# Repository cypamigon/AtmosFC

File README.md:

# AtmosFC

AtmosFC is an open-hardware quadcopter flight controller designed in KiCad. Powered by an STM32G4 MCU, it integrates high-performance sensors and peripherals, and is fully compatible with Betaflight (≥ 4.5).

## Table of Contents
- [Features](#features)
- [Input / Output](#input--output)
- [Hardware Architecture](#hardware-architecture)
- [Flashing Betaflight](#flashing-betaflight)
- [Notes](#notes)
- [Gallery](#gallery)
- [Repository Structure](#repository-structure)
- [License](#license)

## Features

- **MCU**: STM32G473CEU6
- **IMU**: ICM-468-P
- **Barometer**: DPS-386
- **OSD**: MAX7456 for analog on-screen display
- **Blackbox**: 32MB onboard flash memory for log recording
- **Power input**: Up to 8S
    > ⚠️   The board has been tested with 6S LiPo batteries. The onboard MAX25232 buck regulator can theoretically support up to 36 V (~ 8S LiPo), but this has not been tested. Use higher voltages at your own risk.
- **Power monitoring**: Battery voltage and current sensing
- **Status indicators**: Green, Blue, and Amber LEDs
- **Dimensions**: 40x40mm
- **Mounting holes**: 30.5×30.5 mm (M4 holes for silicone inserts with M3 screws)
- **Weight**: 8.2g

## Input / Output 

- **USB connector**: USB Type-C
- **Motor outputs**: x4
- **ESC**: Current sensing and telemetry
- **UARTs**: x3
- **I2C**: Yes
- **Video Input / Video Output with OSD** 
- **5V outputs**: up to 3A total 
- **Buzzer output**

## Hardware Architecture

The block diagram below shows the main hardware components and their interconnections.

##  Flashing Betaflight

AtmosFC runs **Betaflight ≥ 4.5**. You can either flash the precompiled Betaflight 4.5 firmware or build the latest from source.

### Option 1 – Using the provided firmware
1. Open **Betaflight Configurator**.  
   If you don’t have it installed, get the latest version here : [Betaflight Configurator Releases](https://github.com/betaflight/betaflight-configurator/releases/latest)
3. Connect AtmosFC via USB-C.
4. If required, enter DFU mode (hold the BOOT button while plugging in USB).
5. In the Betaflight Configurator, go to **Firmware Flasher → Load firmware [Local]** and select the file `betaflight_4.5.0_ATMOSFC.hex` in `betaflight_config/`.
6. Click **Flash Firmware** and wait for the board to reboot.

### Option 2 – Building from Source

1. Clone the [Betaflight Repository](https://github.com/betaflight/betaflight) and install the required toolchain. Follow the official setup guide for your OS : [Betaflight Building Docs](https://betaflight.com/docs/category/building).
2. In the Betaflight root directory, update the target list by running:
```
> make configs
```
3. Add the AtmosFC board configuration by copying the folder `betaflight_config/ATMOSFC/` into `betaflight/src/config/configs`.
4. Build the firmware for AtmosFC target.
```
> make ATMOSFC
```
5. The compiled `.hex` file will be located under `betaflight/obj/`.
Flash it using **Betaflight Configurator** (follow the steps from Option 1).

## Notes 
- The board has been **successfully tested with Betaflight 4.5**. All basic functions, including motor outputs, sensors, LEDs, were working correctly.
- **I did not test the OSD feature**, as I was flying using digital FPV goggles instead of analog video.
- There is a small **voltage drop on the VBAT measurement** (~0.2-0.3V) due to the Schottky diode used for reverse polarity protection.  
  - This can be compensated either by applying a software offset in Betaflight, or by using an alternative reverse polarity protection method, such as a MOSFET-based circuit

## Gallery

<p align="center">
  
    <br>
  
    <br>
  
    <br>
  
    <br>
  
</p>

## Repository Structure

The repository is organized as follows:

``` bash
├── hardware/             
│   ├── atmos_fc/           # KiCad project files (.kicad_pcb, .sch, etc.)  
│   ├── assembly/           # Fabrication files (Gerber, BOM)
│   └── lib/                # Custom footprints, symbols, 3D models
├── betaflight_config/
│   ├── ATMOSFC/            # Board configuration for Betaflight ≥ 4.5
│   └── betaflight_4.5.0_ATMOSFC.hex    # Precompiled Betaflight 4.5 firmware
├── documentation/          # Schematic (.pdf), images, logo, block diagram
└── README.md
```

##  License

This project is released under the **[MIT License](LICENSE.txt)**.  
You are free to use, modify, and distribute it.

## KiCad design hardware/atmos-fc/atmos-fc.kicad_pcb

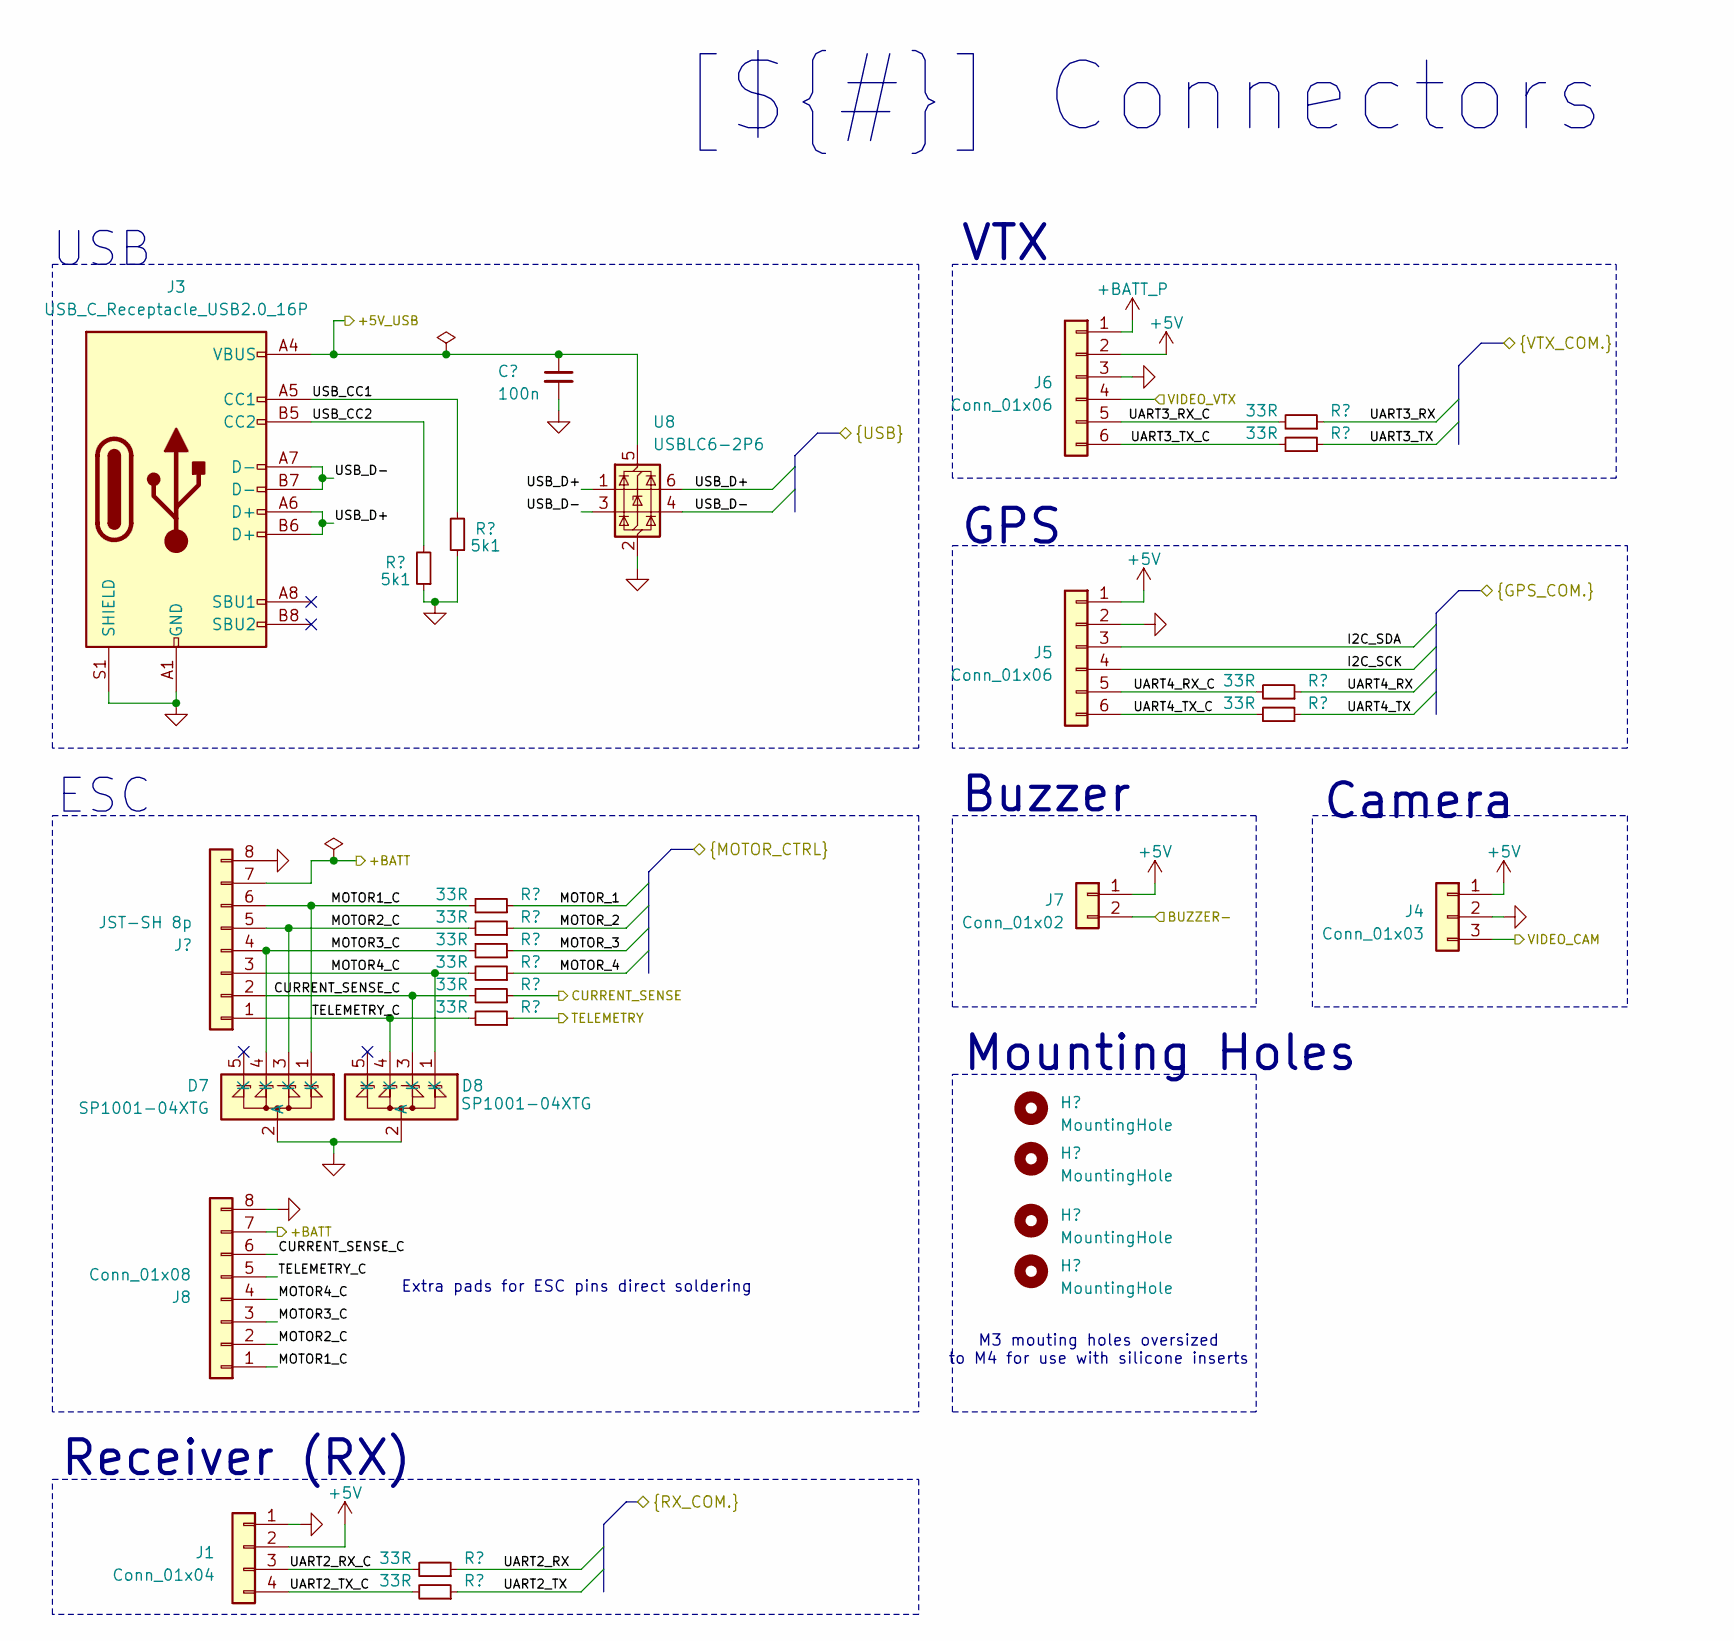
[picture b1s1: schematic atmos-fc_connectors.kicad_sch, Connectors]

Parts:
C34: 100n; C_0402_1005Metric; Mfr Part Number MSASE105SB7104KFNA01
D7, D8: SP1001-04XTG; SOT-553; Mfr Part Number SP1001-04XTG
H1, H2, H3, H4: MountingHole; MountingHole_4.3mm_M4
J1: Conn_01x04; SolderWirePads-2x2
J2: JST-SH 8p; JST_SR_SM08B-SRSS-TB; Mfr Part Number SM08B-SRSS-TB
J3: USB_C_Receptacle_USB2.0_16P; USB_C_Receptacle_GCT_USB4105-xx-A_16P_TopMnt_Horizontal; Mfr Part Number USB4105-GF-A
J4: Conn_01x03; SolderWirePads-1x3
J5, J6: Conn_01x06; SolderWirePads-1x6
J7: Conn_01x02; SolderWirePads-2x1
J8: Conn_01x08; SolderWirePads-2x4
R25, R26: 5k1; R_0402_1005Metric; Mfr Part Number CRCW04025K10FKED
R27, R28, R29, R30, R31, R32, R33, R34, R35, R36, R37, R38: 33R; R_0402_1005Metric; Mfr Part Number CRCW040220K0FKED
U8: USBLC6-2P6; SOT-666; Mfr Part Number USBLC6-2P6

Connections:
+5V: J1.2, J4.1, J5.1, J6.2, J7.1; also elsewhere on the board
+BATT_P: J6.1; also elsewhere on the board
/Connectors/+5V_USB: C34.1, J3.A4 (VBUS), J3.A9 (VBUS), J3.B4 (VBUS), J3.B9 (VBUS), U8.5 (VBUS); also elsewhere on the board
/Connectors/+BATT: J2.7, J8.7; also elsewhere on the board
/Connectors/BUZZER-: J7.2; also elsewhere on the board
/Connectors/CURRENT_SENSE: R31.1; also elsewhere on the board
/Connectors/CURRENT_SENSE_C: D8.3 (K), J2.2, J8.6, R31.2
/Connectors/I2C_SCK: J5.4; also elsewhere on the board
/Connectors/I2C_SDA: J5.3; also elsewhere on the board
/Connectors/MOTOR1_C: D7.1 (K), J2.6, J8.1, R27.2
/Connectors/MOTOR2_C: D7.3 (K), J2.5, J8.2, R28.2
/Connectors/MOTOR3_C: D7.4 (K), J2.4, J8.3, R29.2
/Connectors/MOTOR4_C: D8.1 (K), J2.3, J8.4, R30.2
/Connectors/MOTOR_1: R27.1; also elsewhere on the board
/Connectors/MOTOR_2: R28.1; also elsewhere on the board
/Connectors/MOTOR_3: R29.1; also elsewhere on the board
/Connectors/MOTOR_4: R30.1; also elsewhere on the board
/Connectors/TELEMETRY: R32.1; also elsewhere on the board
/Connectors/TELEMETRY_C: D8.4 (K), J2.1, J8.5, R32.2
/Connectors/UART2_RX: R33.1; also elsewhere on the board
/Connectors/UART2_RX_C: J1.3, R33.2
/Connectors/UART2_TX: R34.1; also elsewhere on the board
/Connectors/UART2_TX_C: J1.4, R34.2
/Connectors/UART3_RX: R37.1; also elsewhere on the board
/Connectors/UART3_RX_C: J6.5, R37.2
/Connectors/UART3_TX: R38.1; also elsewhere on the board
/Connectors/UART3_TX_C: J6.6, R38.2
/Connectors/UART4_RX: R35.1; also elsewhere on the board
/Connectors/UART4_RX_C: J5.5, R35.2
/Connectors/UART4_TX: R36.1; also elsewhere on the board
/Connectors/UART4_TX_C: J5.6, R36.2
/Connectors/USB_CC1: J3.A5 (CC1), R26.2
/Connectors/USB_CC2: J3.B5 (CC2), R25.2
/Connectors/USB_D+: J3.A6 (D+), J3.B6 (D+), U8.1 (I/O1), U8.6 (I/O1); also elsewhere on the board
/Connectors/USB_D-: J3.A7 (D-), J3.B7 (D-), U8.3 (I/O2), U8.4 (I/O2); also elsewhere on the board
/Connectors/VIDEO_CAM: J4.3; also elsewhere on the board
/Connectors/VIDEO_VTX: J6.4; also elsewhere on the board
GND: C34.2, D7.2 (A), D8.2 (A), J1.1, J2.8, J3.A1 (GND), J3.A12 (GND), J3.B1 (GND), J3.B12 (GND), J3.S1 (SHIELD), J4.2, J5.2, J6.3, J8.8, R25.1, R26.1, U8.2 (GND); also elsewhere on the board

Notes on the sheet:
[${#}] ${TITLE}
Camera
M3 mouting holes oversized to M4 for use with silicone inserts
Mounting Holes
Receiver (RX)
ESC
Buzzer
VTX
Extra pads for ESC pins direct soldering
GPS
USB

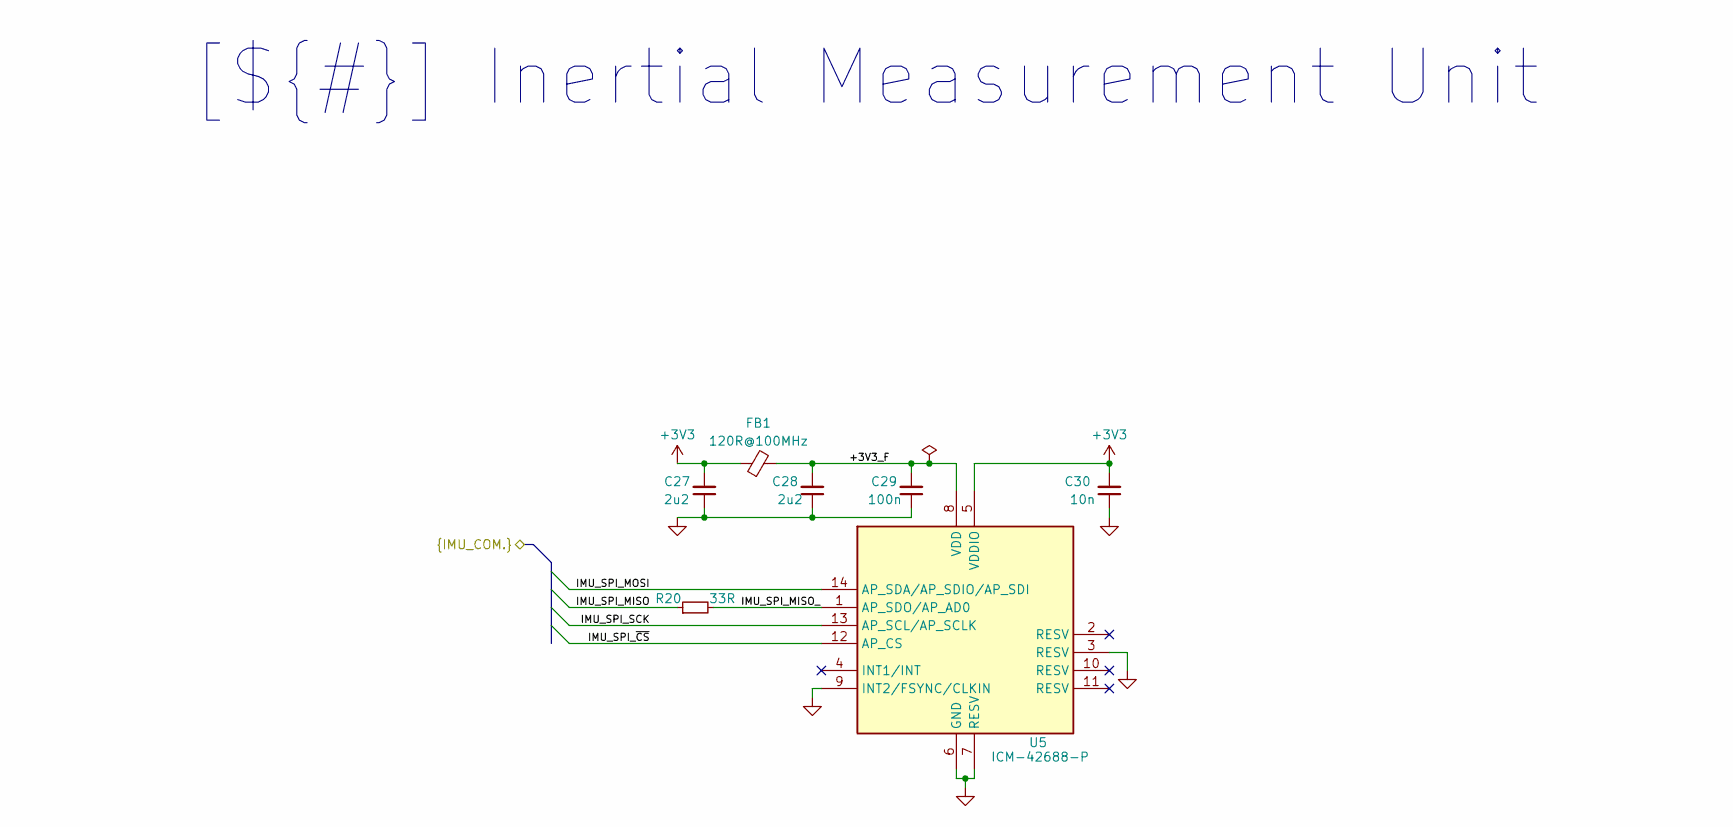
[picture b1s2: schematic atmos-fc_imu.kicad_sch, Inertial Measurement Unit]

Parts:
C27, C28: 2u2; C_0402_1005Metric; Mfr Part Number GRM155C71A225KE11D
C29: 100n; C_0402_1005Metric; Mfr Part Number MSASE105SB7104KFNA01
C30: 10n; C_0402_1005Metric; Mfr Part Number GRM1555C1E103GE01D
FB1: 120R@100MHz; L_0402_1005Metric; Mfr Part Number BLM15PX121BH1D
R20: 33R; R_0402_1005Metric; Mfr Part Number CRCW040220K0FKED
U5: ICM-42688-P; Mfr Part Number ICM-42688-P

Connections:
+3V3: C27.2, C30.2, FB1.1, U5.5 (VDDIO); also elsewhere on the board
/IMU/+3V3_F: C28.2, C29.2, FB1.2, U5.8 (VDD)
/IMU/IMU_INT: U5.4 (INT1/INT); also elsewhere on the board
/IMU/IMU_SPI_MISO: R20.1; also elsewhere on the board
/IMU/IMU_SPI_MISO_: R20.2, U5.1 (AP_SDO/AP_AD0)
/IMU/IMU_SPI_MOSI: U5.14 (AP_SDA/AP_SDIO/AP_SDI); also elsewhere on the board
/IMU/IMU_SPI_SCK: U5.13 (AP_SCL/AP_SCLK); also elsewhere on the board
/IMU/IMU_SPI_~CS: U5.12 (AP_CS); also elsewhere on the board
GND: C27.1, C28.1, C29.1, C30.1, U5.3 (RESV), U5.6 (GND), U5.7 (RESV), U5.9 (INT2/FSYNC/CLKIN); also elsewhere on the board

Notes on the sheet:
[${#}] ${TITLE}

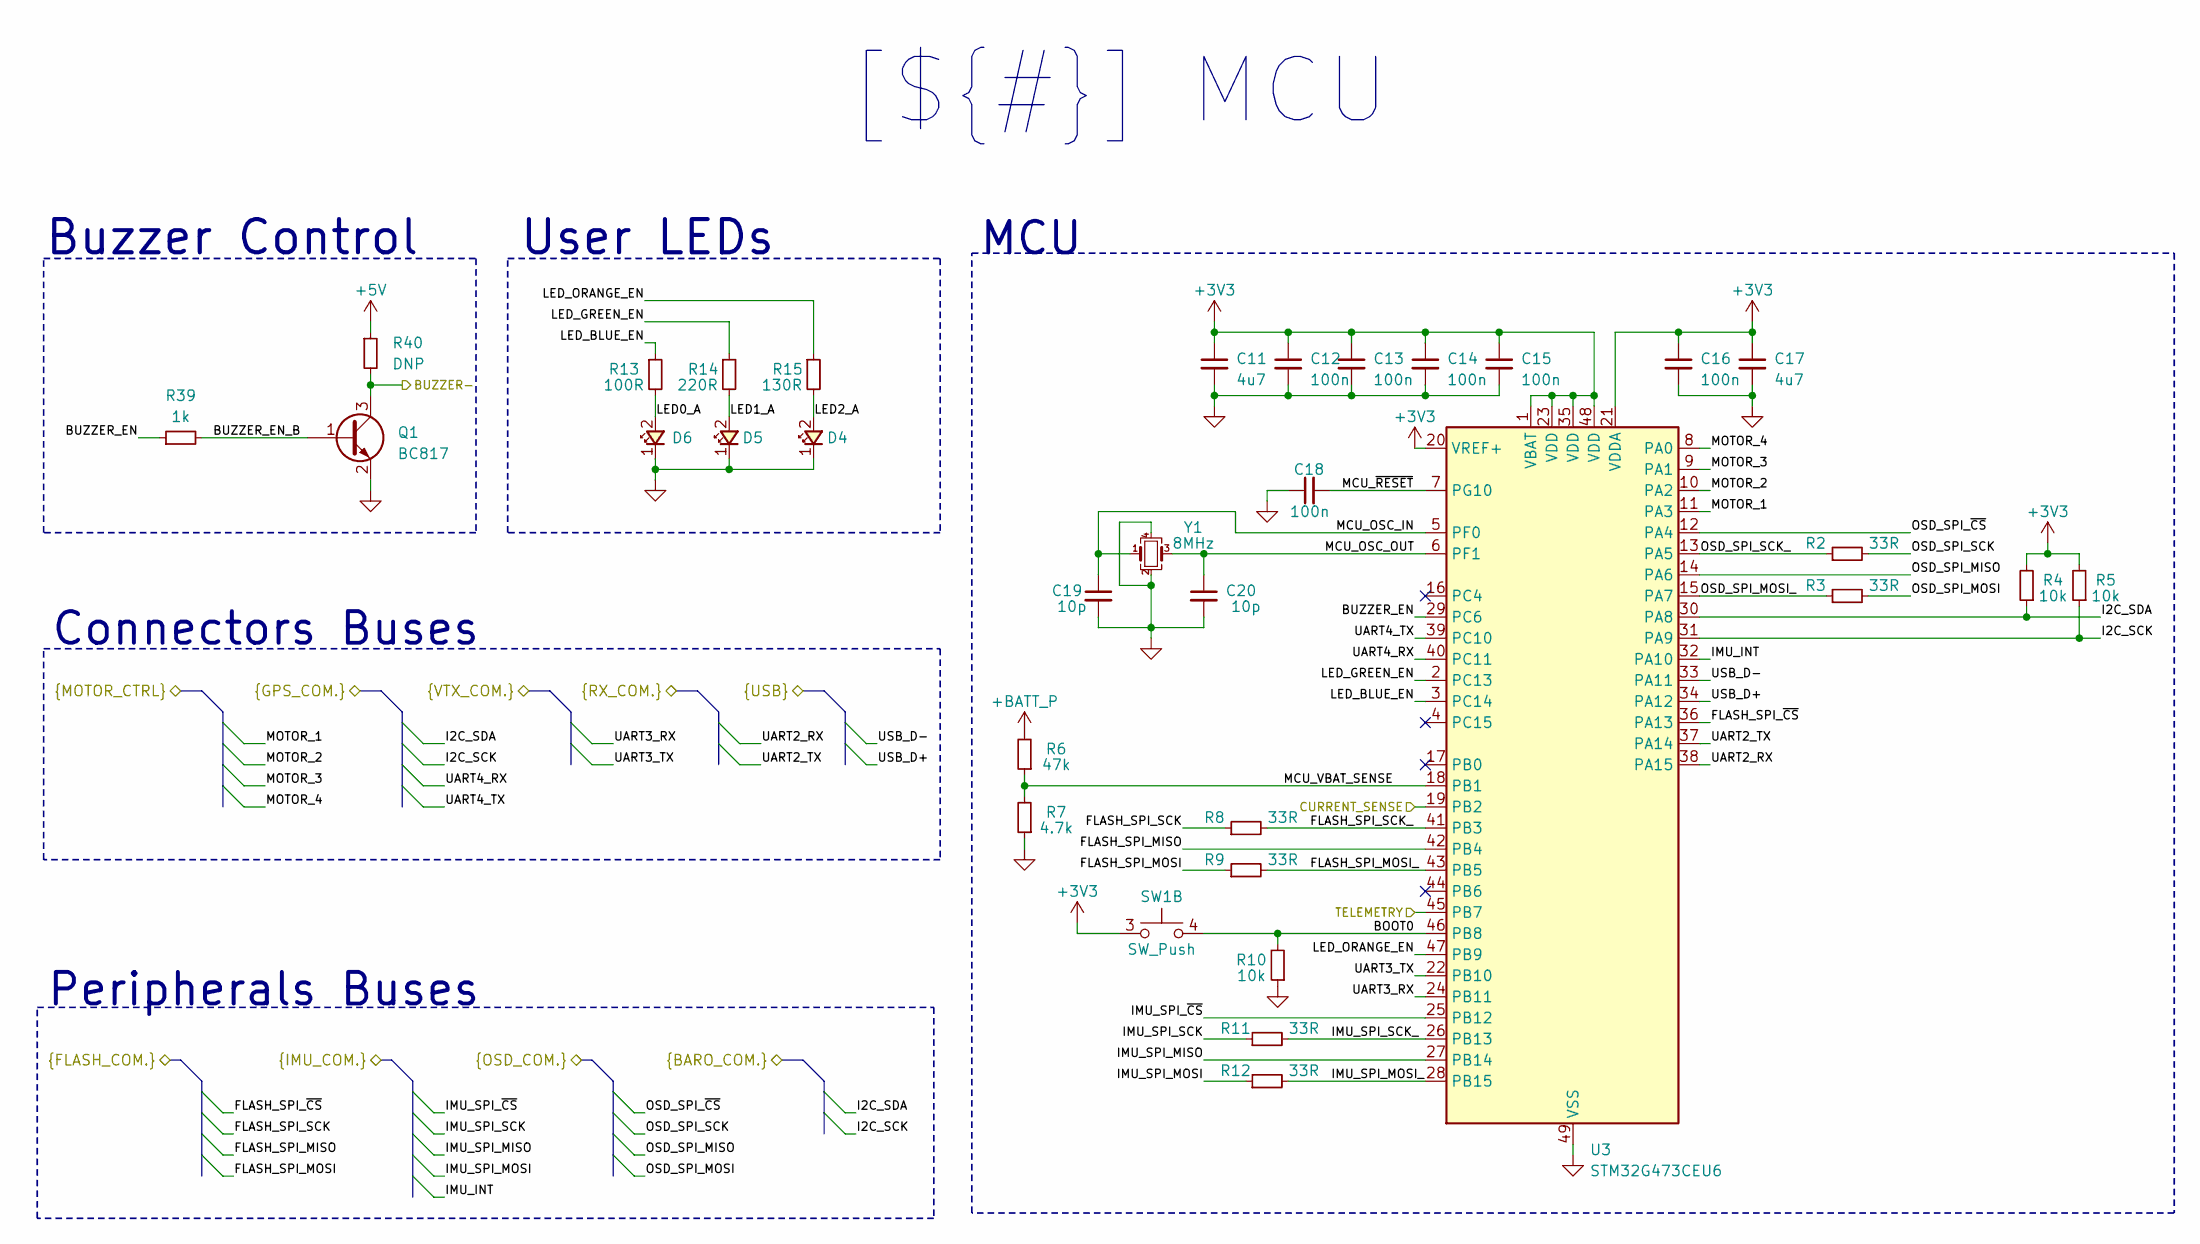
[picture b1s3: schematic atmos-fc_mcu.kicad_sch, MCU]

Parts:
C11, C17: 4u7; C_0603_1608Metric; Mfr Part Number GRM188Z71C475KE21J
C12, C13, C14, C15, C16, C18: 100n; C_0402_1005Metric; Mfr Part Number MSASE105SB7104KFNA01
C19, C20: 10p; C_0402_1005Metric; Mfr Part Number GRM1555C1H100JA01D
D4: LED_0603_1608Metric; Mfr Part Number LO Q976-PS-25
D5: LED_0603_1608Metric; Mfr Part Number LT Q39G-Q1OO-25-1
D6: LED_0603_1608Metric; Mfr Part Number LB Q39G-N1OO-35-1
Q1: BC817; DFN1010D-3; Mfr Part Number BC817-40QBH-QZ
R2, R3, R8, R9, R11, R12: 33R; R_0402_1005Metric; Mfr Part Number CRCW040220K0FKED
R4, R5, R10: 10k; R_0402_1005Metric; Mfr Part Number CRCW040210K0FKEDC
R6: 47k; R_0402_1005Metric; Mfr Part Number CRCW040247K0FKEDC
R7: 4.7k; R_0402_1005Metric; Mfr Part Number CRCW04024K70FKEDC
R13: 100R; R_0402_1005Metric; Mfr Part Number CRCW0402100RFKEDC
R14: 220R; R_0402_1005Metric; Mfr Part Number CRCW0402220RFKED
R15: 130R; R_0402_1005Metric; Mfr Part Number CRCW0402130RFKEDC
R39: 1k; R_0402_1005Metric; Mfr Part Number CRCW04021K00FKED
R40: DNP; R_0402_1005Metric
SW1: SW_Push; Wurth_436331045822; Mfr Part Number 436331045822
U3: STM32G473CEU6; QFN-48-1EP_7x7mm_P0.5mm_EP5.6x5.6mm; Mfr Part Number STM32G473CEU6
Y1: 8MHz; Crystal_SMD_ECS_ECX33_4Pin_3.2x2.5mm; Mfr Part Number ECS-80-10-33-CGN-TR3

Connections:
+3V3: C11.1, C12.1, C13.1, C14.1, C15.1, C16.1, C17.1, R4.2, R5.2, SW1.3 (C), U3.1 (VBAT), U3.20 (VREF+), U3.21 (VDDA), U3.23 (VDD), U3.35 (VDD), U3.48 (VDD); also elsewhere on the board
+5V: R40.1; also elsewhere on the board
+BATT_P: R6.2; also elsewhere on the board
/Connectors/BUZZER-: Q1.3 (C), R40.2; also elsewhere on the board
/Connectors/CURRENT_SENSE: U3.19 (PB2); also elsewhere on the board
/Connectors/I2C_SCK: R5.1, U3.31 (PA9); also elsewhere on the board
/Connectors/I2C_SDA: R4.1, U3.30 (PA8); also elsewhere on the board
/Connectors/MOTOR_1: U3.11 (PA3); also elsewhere on the board
/Connectors/MOTOR_2: U3.10 (PA2); also elsewhere on the board
/Connectors/MOTOR_3: U3.9 (PA1); also elsewhere on the board
/Connectors/MOTOR_4: U3.8 (PA0); also elsewhere on the board
/Connectors/TELEMETRY: U3.45 (PB7); also elsewhere on the board
/Connectors/UART2_RX: U3.38 (PA15); also elsewhere on the board
/Connectors/UART2_TX: U3.37 (PA14); also elsewhere on the board
/Connectors/UART3_RX: U3.24 (PB11); also elsewhere on the board
/Connectors/UART3_TX: U3.22 (PB10); also elsewhere on the board
/Connectors/UART4_RX: U3.40 (PC11); also elsewhere on the board
/Connectors/UART4_TX: U3.39 (PC10); also elsewhere on the board
/Connectors/USB_D+: U3.34 (PA12); also elsewhere on the board
/Connectors/USB_D-: U3.33 (PA11); also elsewhere on the board
/Flash Memory/FLASH_SPI_MISO: U3.42 (PB4); also elsewhere on the board
/Flash Memory/FLASH_SPI_MOSI: R9.1; also elsewhere on the board
/Flash Memory/FLASH_SPI_SCK: R8.1; also elsewhere on the board
/Flash Memory/FLASH_SPI_~CS: U3.36 (PA13); also elsewhere on the board
/IMU/IMU_INT: U3.32 (PA10); also elsewhere on the board
/IMU/IMU_SPI_MISO: U3.27 (PB14); also elsewhere on the board
/IMU/IMU_SPI_MOSI: R12.1; also elsewhere on the board
/IMU/IMU_SPI_SCK: R11.1; also elsewhere on the board
/IMU/IMU_SPI_~CS: U3.25 (PB12); also elsewhere on the board
/MCU/BOOT0: R10.2, SW1.4 (D), U3.46 (PB8)
/MCU/BUZZER_EN: R39.1, U3.29 (PC6)
/MCU/BUZZER_EN_B: Q1.1 (B), R39.2
/MCU/FLASH_SPI_MOSI_: R9.2, U3.43 (PB5)
/MCU/FLASH_SPI_SCK_: R8.2, U3.41 (PB3)
/MCU/IMU_SPI_MOSI_: R12.2, U3.28 (PB15)
/MCU/IMU_SPI_SCK_: R11.2, U3.26 (PB13)
/MCU/LED0_A: D6.2, R13.2
/MCU/LED1_A: D5.2, R14.2
/MCU/LED2_A: D4.2, R15.2
/MCU/LED_BLUE_EN: R13.1, U3.3 (PC14)
/MCU/LED_GREEN_EN: R14.1, U3.2 (PC13)
/MCU/LED_ORANGE_EN: R15.1, U3.47 (PB9)
/MCU/MCU_OSC_IN: C19.1, U3.5 (PF0), Y1.1
/MCU/MCU_OSC_OUT: C20.1, U3.6 (PF1), Y1.3
/MCU/MCU_VBAT_SENSE: R6.1, R7.2, U3.18 (PB1)
/MCU/MCU_~RESET: C18.2, U3.7 (PG10)
/MCU/OSD_SPI_MISO: U3.14 (PA6); also elsewhere on the board
/MCU/OSD_SPI_MOSI: R3.2; also elsewhere on the board
/MCU/OSD_SPI_MOSI_: R3.1, U3.15 (PA7)
/MCU/OSD_SPI_SCK: R2.2; also elsewhere on the board
/MCU/OSD_SPI_SCK_: R2.1, U3.13 (PA5)
/MCU/OSD_SPI_~CS: U3.12 (PA4); also elsewhere on the board
GND: C11.2, C12.2, C13.2, C14.2, C15.2, C16.2, C17.2, C18.1, C19.2, C20.2, D4.1, D5.1, D6.1, Q1.2 (E), R7.1, R10.1, U3.49 (VSS), Y1.2, Y1.4; also elsewhere on the board

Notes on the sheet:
[${#}] ${TITLE}
MCU
Peripherals Buses
Buzzer Control
Connectors Buses
User LEDs

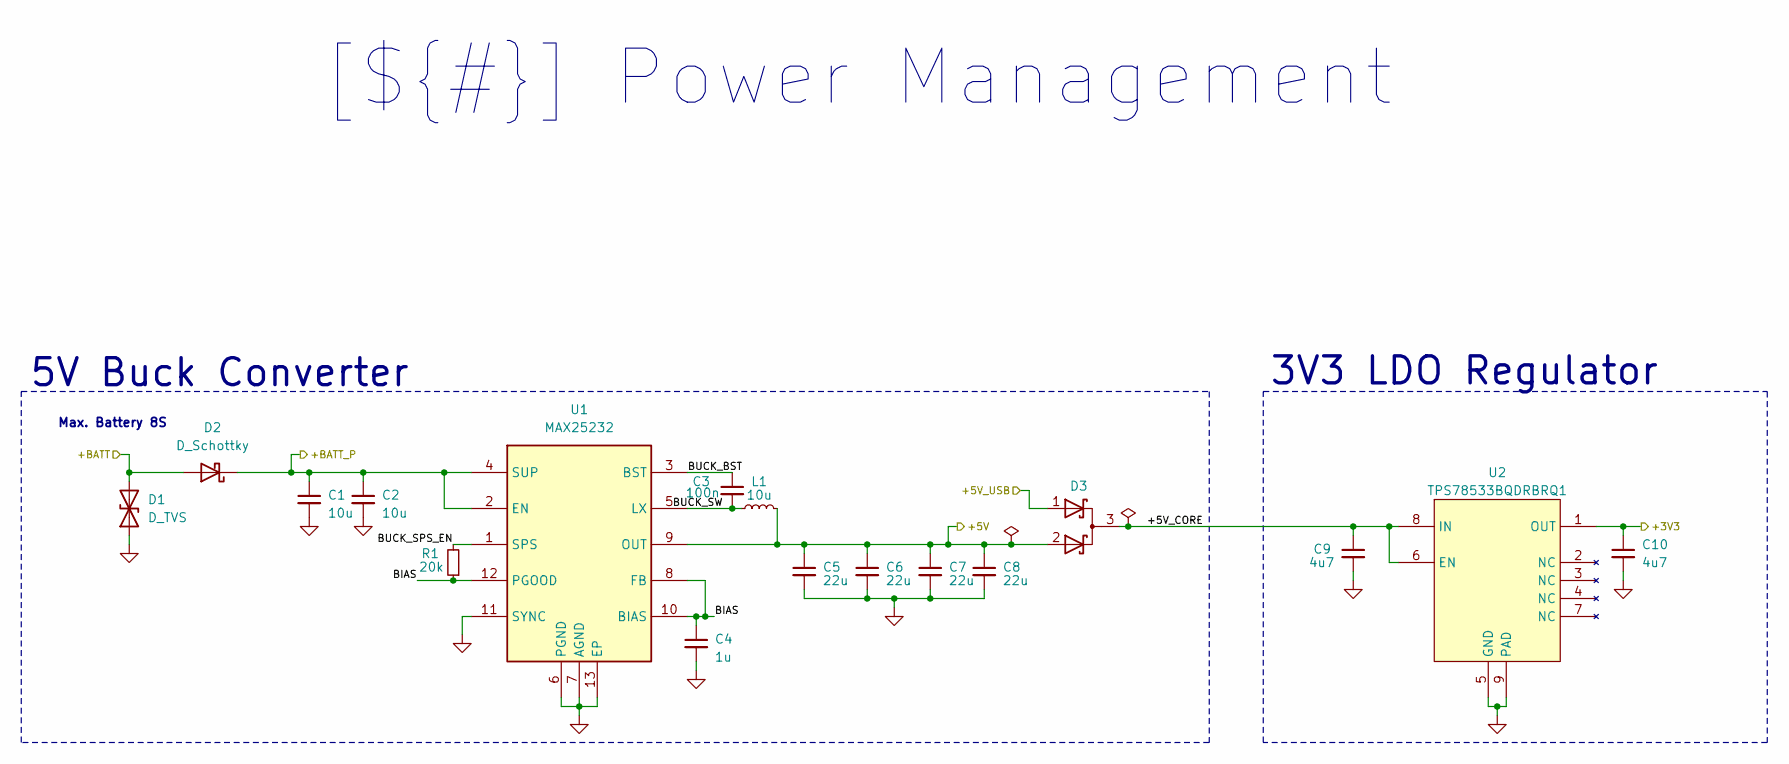
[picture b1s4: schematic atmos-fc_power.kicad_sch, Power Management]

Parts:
C1, C2: 10u; C_1206_3216Metric; Mfr Part Number MCJCG31LBB7106KTPA01
C3: 100n; C_0402_1005Metric; Mfr Part Number MSASE105SB7104KFNA01
C4: 1u; C_0603_1608Metric; Mfr Part Number MSAST168SB7105KTNA01
C5, C6, C7, C8: 22u; C_1206_3216Metric; Mfr Part Number MSASE31LBB7226MTNA01
C9, C10: 4u7; C_0603_1608Metric; Mfr Part Number GRM188Z71C475KE21J
D1: D_TVS; D_SOD-882; Mfr Part Number PESD30VF1BBL-QYL
D2: D_Schottky; DFN3820A; Mfr Part Number V7N103HM3/I
D3: PMEG2020CPASX; HUSON-3-1EP_2x2mm_P1.3mm_EP1.1x1.6mm; Mfr Part Number PMEG2020CPASX
L1: 10u; L_Bourns_SRP5030CC; Mfr Part Number SRP5030CC-100M
R1: 20k; R_0402_1005Metric; Mfr Part Number CRCW040220K0FKED
U1: MAX25232; Maxim_TDFN-12-1EP_3x3mm_P0.5mm_EP1.7x2.5mm_ThermalVias; Mfr Part Number MAX25232ATCD_V+
U2: TPS78533BQDRBRQ1; VSON-8-1EP_3x3mm_P0.65mm_EP1.65x2.4mm_ThermalVias; Mfr Part Number TPS78533BQWDRBRQ1

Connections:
+3V3: C10.1, U2.1 (OUT); also elsewhere on the board
+5V: C5.1, C6.1, C7.1, C8.1, D3.2 (K), L1.2, U1.9 (OUT); also elsewhere on the board
+BATT_P: C1.1, C2.1, D2.1 (K), U1.2 (EN), U1.4 (SUP); also elsewhere on the board
/Connectors/+5V_USB: D3.1 (K); also elsewhere on the board
/Connectors/+BATT: D1.2 (A2), D2.2 (A); also elsewhere on the board
/Power Management/+5V_CORE: C9.1, D3.3 (A), U2.6 (EN), U2.8 (IN)
/Power Management/BIAS: C4.1, R1.1, U1.8 (FB), U1.10 (BIAS), U1.12 (PGOOD)
/Power Management/BUCK_BST: C3.1, U1.3 (BST)
/Power Management/BUCK_SPS_EN: R1.2, U1.1 (SPS)
/Power Management/BUCK_SW: C3.2, L1.1, U1.5 (LX)
GND: C1.2, C2.2, C4.2, C5.2, C6.2, C7.2, C8.2, C9.2, C10.2, D1.1 (A1), U1.6 (PGND), U1.7 (AGND), U1.11 (SYNC), U1.13 (EP), U2.5 (GND), U2.9 (PAD); also elsewhere on the board

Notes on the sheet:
[${#}] ${TITLE}
5V Buck Converter
3V3 LDO Regulator
Max. Battery 8S

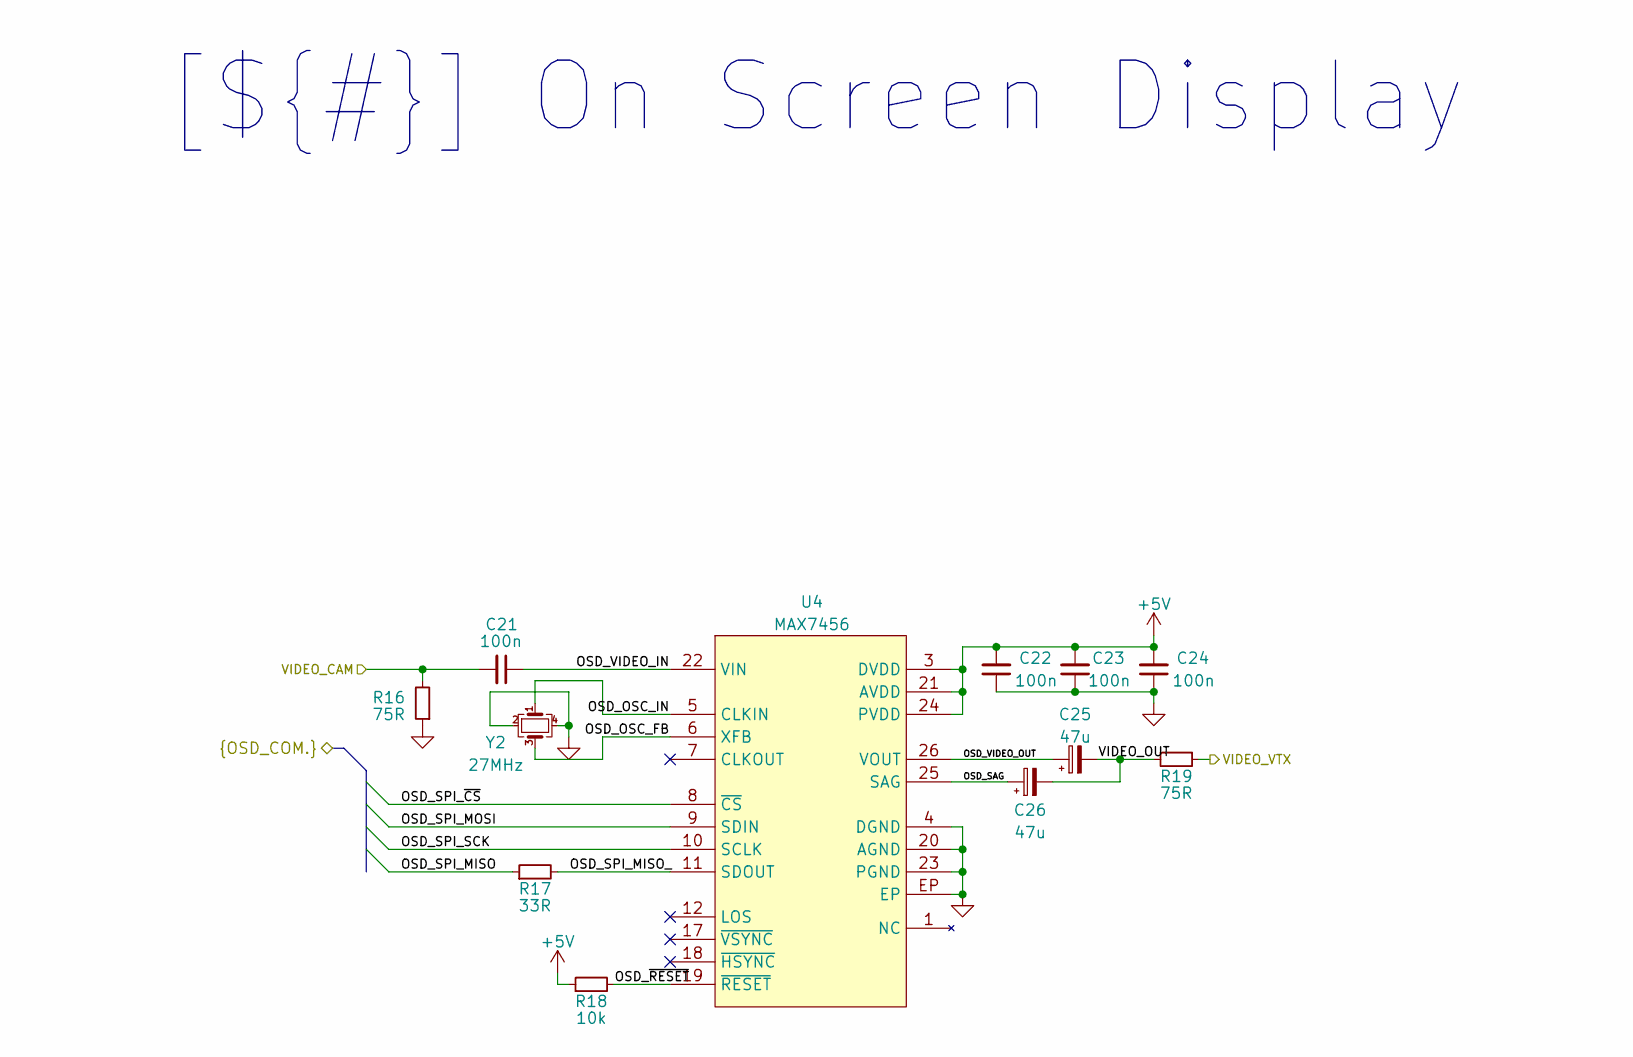
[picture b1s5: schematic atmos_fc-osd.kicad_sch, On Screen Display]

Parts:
C21, C22, C23, C24: 100n; C_0402_1005Metric; Mfr Part Number MSASE105SB7104KFNA01
C25, C26: 47u; CP_EIA-2012-12_Kemet-R; Mfr Part Number F981A476MSAAS1
R16, R19: 75R; R_0402_1005Metric; Mfr Part Number CRCW040275R0FKED
R17: 33R; R_0402_1005Metric; Mfr Part Number CRCW040220K0FKED
R18: 10k; R_0402_1005Metric; Mfr Part Number CRCW040210K0FKEDC
U4: MAX7456; TSSOP-28-1EP_4.4x9.7mm_P0.65mm_EP3.1x6.9mm; Mfr Part Number MAX7456EUI+
Y2: 27MHz; Crystal_SMD_2016-4Pin_2.0x1.6mm; Mfr Part Number CX2016SA27000D0GSSCC

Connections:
+5V: C22.2, C23.2, C24.2, R18.1, U4.3 (DVDD), U4.21 (AVDD), U4.24 (PVDD); also elsewhere on the board
/Connectors/VIDEO_CAM: C21.2, R16.2; also elsewhere on the board
/Connectors/VIDEO_VTX: R19.1; also elsewhere on the board
/MCU/OSD_SPI_MISO: R17.1; also elsewhere on the board
/MCU/OSD_SPI_MOSI: U4.9 (SDIN); also elsewhere on the board
/MCU/OSD_SPI_SCK: U4.10 (SCLK); also elsewhere on the board
/MCU/OSD_SPI_~CS: U4.8 (~CS); also elsewhere on the board
/OSD/OSD_OSC_FB: U4.6 (XFB), Y2.3
/OSD/OSD_OSC_IN: U4.5 (CLKIN), Y2.1
/OSD/OSD_SAG: C26.1, U4.25 (SAG)
/OSD/OSD_SPI_MISO_: R17.2, U4.11 (SDOUT)
/OSD/OSD_VIDEO_IN: C21.1, U4.22 (VIN)
/OSD/OSD_VIDEO_OUT: C25.1, U4.26 (VOUT)
/OSD/OSD_~RESET: R18.2, U4.19 (~RESET)
/OSD/VIDEO_OUT: C25.2, C26.2, R19.2
GND: C22.1, C23.1, C24.1, R16.1, U4.4 (DGND), U4.20 (AGND), U4.23 (PGND), U4.EP, Y2.2, Y2.4; also elsewhere on the board

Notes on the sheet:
[${#}] ${TITLE}

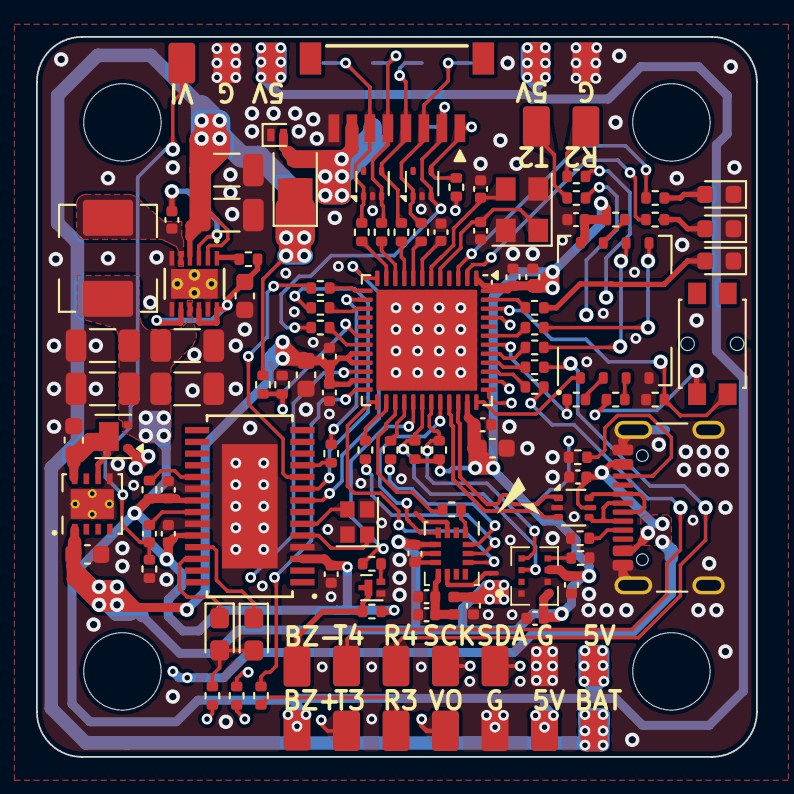
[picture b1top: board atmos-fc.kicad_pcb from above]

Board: 4 copper layers, 40.0 x 40.0 mm, 108 parts (1 on the bottom side), 90 nets.

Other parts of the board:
C31, C32, C33: 100n; C_0402_1005Metric
R21: 33R; R_0402_1005Metric
R22, R23, R24: 47k; R_0402_1005Metric
U6: W25Q256JVE; WSON-8-1EP_8x6mm_P1.27mm
U7: DPS368XTSA1; Infineon_PG-VLGA-8-2

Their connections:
+3V3: C31.2, C32.2, C33.2, R22.1, R23.1, U6.8 (VCC), U7.6 (VDDIO), U7.8 (VDD); also elsewhere on the board
/Barometer/BARO_SDO: R24.2, U7.5 (SDO)
/Connectors/I2C_SCK: U7.4 (SCK); also elsewhere on the board
/Connectors/I2C_SDA: U7.3 (SDI); also elsewhere on the board
/Flash Memory/FLASH_SPI_MISO: R21.1; also elsewhere on the board
/Flash Memory/FLASH_SPI_MISO_: R21.2, U6.2 (IO1)
/Flash Memory/FLASH_SPI_MOSI: U6.5 (IO0); also elsewhere on the board
/Flash Memory/FLASH_SPI_SCK: U6.6 (CLK); also elsewhere on the board
/Flash Memory/FLASH_SPI_~CS: U6.1 (~CS); also elsewhere on the board
/Flash Memory/FLASH_~HOLD: R23.2, U6.7 (IO3)
/Flash Memory/FLASH_~WP: R22.2, U6.3 (IO2)
GND: C31.1, C32.1, C33.1, R24.1, U6.4 (GND), U7.1 (GND), U7.7 (GND); also elsewhere on the board

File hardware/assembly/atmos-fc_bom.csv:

"Reference","Value","Qty","Description","Manufacturer","Mfr Part Number"
"C19,C20","10p","2","Multilayer Ceramic Capacitors MLCC - SMD/SMT 10 pF 50 VDC 5% 0402 C0G (NP0)","Murata Electronics","GRM1555C1H100JA01D"
"C30","10n","1","Multilayer Ceramic Capacitors MLCC - SMD/SMT 0.01 uF 25 VDC 2% 0402 C0G (NP0)","Murata Electronics","GRM1555C1E103GE01D"
"C3,C12,C13,C14,C15,C16,C18,C21,C22,C23,C24,C29,C31,C32,C33,C34","100n","16","Multilayer Ceramic Capacitors MLCC - SMD/SMT 16V 0.1uF X7R 0402 10 %","TAIYO YUDEN","MSASE105SB7104KFNA01"
"C4","1u","1","Multilayer Ceramic Capacitors MLCC - SMD/SMT 25V 1uF X7R 0603 10 %","TAIYO YUDEN","MSAST168SB7105KTNA01"
"C1,C2","10u","2","Multilayer Ceramic Capacitors MLCC - SMD/SMT 35V 10uF X7R 1206 10 %","TAIYO YUDEN","MCJCG31LBB7106KTPA01"
"L1","10u","1","Power Inductors - SMD Ind,5.7x5.2x2.8mm,10uH+/-20%,2.8A,shd","Bourns","SRP5030CC-100M"
"C5,C6,C7,C8","22u","4","Multilayer Ceramic Capacitors MLCC - SMD/SMT 16V 22uF X7R 1206 20 %","TAIYO YUDEN","MSASE31LBB7226MTNA01"
"C25,C26","47u","2","Tantalum Capacitors - Solid SMD 10V 47uF 0805 Tol +/-20%","KYOCERA AVX","F981A476MSAAS1"
"R2,R3,R8,R9,R11,R12,R17,R20,R21,R27,R28,R29,R30,R31,R32,R33,R34,R35,R36,R37,R38","33R","21","Thick Film Resistors - SMD 1/16watt 33ohms 1% 100ppm","Vishay / Dale","CRCW040220K0FKED"
"R16,R19","75R","2","Thick Film Resistors - SMD 1/16watt 75ohms 1%","Vishay / Dale","CRCW040275R0FKED"
"R13","100R","1","Thick Film Resistors - SMD 1/16watt 100ohms 1% Commercial Use","Vishay / Dale","CRCW0402100RFKEDC"
"R15","130R","1","Thick Film Resistors - SMD 1/16watt 130ohms 1% Commercial Use","Vishay / Dale","CRCW0402130RFKEDC"
"R14","220R","1","Thick Film Resistors - SMD 1/16watt 220ohms 1%","Vishay / Dale","CRCW0402220RFKED"
"R39","1k","1","Thick Film Resistors - SMD 1/16watt 1.0Kohms 1%","Vishay / Dale","CRCW04021K00FKED"
"R7","4.7k","1","Thick Film Resistors - SMD 1/16watt 4.7Kohms 1% Commercial Use","Vishay / Dale","CRCW04024K70FKEDC"
"R4,R5,R10,R18","10k","4","Thick Film Resistors - SMD 1/16watt 10Kohms 1% Commercial Use","Vishay / Dale","CRCW040210K0FKEDC"
"R1","20k","1","Thick Film Resistors - SMD 1/16watt 20Kohms 1%","Vishay / Dale","CRCW040220K0FKED"
"R6,R22,R23,R24","47k","4","Thick Film Resistors - SMD 1/16watt 47Kohms 1% Commercial Use","Vishay / Dale","CRCW040247K0FKEDC"
"Y1","8MHz","1","Crystals 8MHz 10 pF 3225 TOL +/-10, STAB +/-30 ppm, -40 +85 C, 400O","ECS","ECS-80-10-33-CGN-TR3"
"Y2","27MHz","1","Crystals 27MHz 8pF AEC-Q200 2 .05X1.65X.45mm","KYOCERA AVX","CX2016SA27000D0GSSCC"
"FB1","120R@100MHz","1","Ferrite Beads 0402 120ohm 25% 5A AEC-Q200","Murata Electronics","BLM15PX121BH1D"
"C27,C28","2u2","2","Multilayer Ceramic Capacitors MLCC - SMD/SMT 2.2 uF 10 VDC 10% 0402 X7S","Murata Electronics","GRM155C71A225KE11D"
"C9,C10,C11,C17","4u7","4","Multilayer Ceramic Capacitors MLCC - SMD/SMT 4.7 uF 16 VDC 10% 0603 X7R","Murata Electronics","GRM188Z71C475KE21J"
"R25,R26","5k1","2","Thick Film Resistors - SMD 1/16watt 5.1Kohms 1%","Vishay / Dale","CRCW04025K10FKED"
"Q1","BC817","1","Bipolar Transistors - BJT SOT8015 45V .5A NPN GP TRANS","Nexperia","BC817-40QBH-QZ"
"J7","Conn_01x02","1","","",""
"J4","Conn_01x03","1","","",""
"J1","Conn_01x04","1","","",""
"J5,J6","Conn_01x06","2","","",""
"D2","D_Schottky","1","Schottky Diodes & Rectifiers 7A, 100V, DFN3820A TRENCH SKY RECT.","Vishay Semiconductors ","V7N103HM3/I"
"D1","D_TVS","1","ESD Protection Diodes / TVS Diodes ESD 30V BI","Nexperia","PESD30VF1BBL-QYL"
"R40","DNP","1","","",""
"U7","DPS368XTSA1","1","Digital XENSIVTM barometric pressure sensor"," Infineon Technologies","DPS368XTSA1"
"U5","ICM-42688-P","1","High Precision 6-Axis MEMS MotionTrackingTM Device","TDK InvenSense","ICM-42688-P"
"J2","JST-SH 8p","1","Headers & Wire Housings SR HEADER (SMT SIDE)","JST Sales America Inc.","SM08B-SRSS-TB"
"U4","MAX7456","1","Single-Channel Monochrome On-Screen Display with Integrated EEPROM","Analog Devices","MAX7456EUI+"
"U1","MAX25232","1","36V, 3A Mini Buck Converters with 3.5uA IQ","Analog Devices","MAX25232ATCD_V+"
"D3","PMEG2020CPASX","1","Schottky Diodes & Rectifiers RECTIFIER SOT1061/HUSON3","Nexperia","PMEG2020CPASX"
"D7,D8","SP1001-04XTG","2","8pF 15kV Unidirectional TVS Array","Littlefuse","SP1001-04XTG"
"U3","STM32G473CEU6","1","ARM Microcontrollers - MCU Mainstream Arm Cortex-M4 MCU 170MHz 512Kbytes of Flash Math Accel, High Analog","STMicroelectronics","STM32G473CEU6"
"SW1","SW_Push","1","Tactile Switches Tact Switch SMT 1.65mm","Wurth Elektronik","436331045822"
"U2","TPS78533BQDRBRQ1","1","TPS785-Q1 Automotive, 1-A, High-PSRR Low-Dropout Voltage Regulator With High Accuracy and Enable","Texas Instruments","TPS78533BQWDRBRQ1"
"J3","USB_C_Receptacle_USB2.0_16P","1","USB 2.0-only 16P Type-C Receptacle connector","GCT","USB4105-GF-A"
"U8","USBLC6-2P6","1","Very low capacitance ESD protection diode, 2 data-line, SOT-666","STMicroelectronics","USBLC6-2P6"
"U6","W25Q256JVE","1","3V 256M-BIT SERIAL FLASH MEMORY WITH DUAL/QUAD SPI","Winbond","W25Q256JVEIQ "
"D4,D5,D6","~","3","-- valeurs mixtées --","ams OSRAM","-- valeurs mixtées --"

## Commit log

2025-09-02 Add sources files
2025-09-02 Update Hardware Block Diagram
2025-09-02 Change images files
2025-09-02 Add docs
2025-09-03 Improved layout
    Added oversized holes for mounting silicone inserts and improved layout.
2025-09-03 Add GYRO_1_EXTI Pin
2025-09-03 Add soldering pads for ESC
2025-09-04 Added 100n on ADC inputs and improved layout
2025-09-04 Update schematic
